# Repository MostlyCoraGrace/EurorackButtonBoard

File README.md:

# EurorackButtonBoard
 A modular, hot-swappable, and patchable, Eurorack-compatible simrig/buttonboard system.
 
 [Follow development on Hackaday](https://hackaday.io/project/199159-eurorack-buttonboard)

# Special Thanks
- A special thanks has to go [PCBWay](https://pcbway.com/g/odjF56), for providing me with free PCBs (and discounts on PCBs when I ask for too many of them, because this project is *voluminous*).
- I would also like to thank my girlfriend, who gave me enough money to buy the first set of electronics I needed to make version 1 of this project. It was expensive.

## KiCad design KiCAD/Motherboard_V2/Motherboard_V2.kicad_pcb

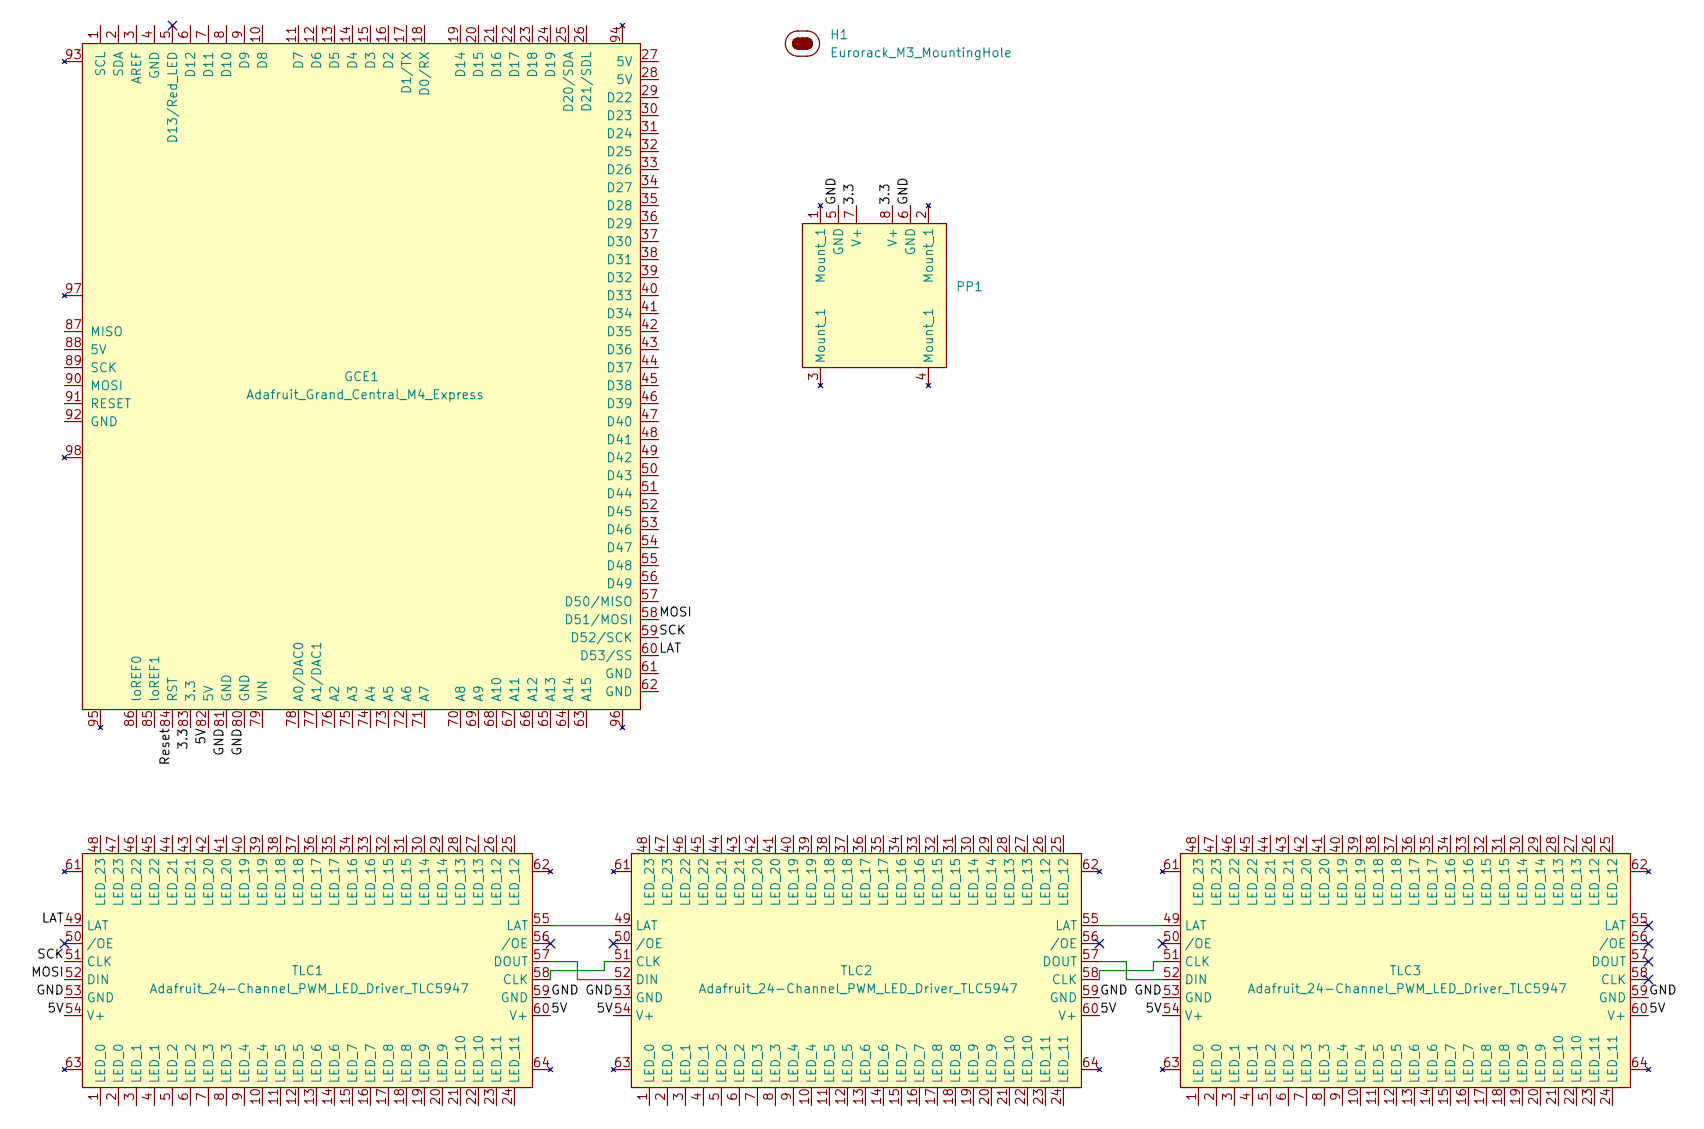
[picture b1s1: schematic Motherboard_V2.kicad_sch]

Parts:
GCE1: Adafruit_Grand_Central_M4_Express
H1: Eurorack_M3_MountingHole; MountingHole_3.2mm_M3
PP1: Adafruit_Perma-Proto_Mint-Tin-Size
TLC1, TLC2, TLC3: Adafruit_24-Channel_PWM_LED_Driver_TLC5947

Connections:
/3.3: GCE1.83 (3.3), PP1.7 (V+), PP1.8 (V+)
/5V: GCE1.82 (5V), TLC1.54 (V+), TLC1.60 (V+), TLC2.54 (V+), TLC2.60 (V+), TLC3.54 (V+), TLC3.60 (V+)
/GND: GCE1.80 (GND), GCE1.81 (GND), PP1.5 (GND), PP1.6 (GND), TLC1.53 (GND), TLC1.59 (GND), TLC2.53 (GND), TLC2.59 (GND), TLC3.53 (GND), TLC3.59 (GND)
/LAT: GCE1.60 (D53/SS), TLC1.49 (LAT)
/MOSI: GCE1.58 (D51/MOSI), TLC1.52 (DIN)
/Reset: GCE1.84 (RST)
/SCK: GCE1.59 (D52/SCK), TLC1.51 (CLK)
unnamed: TLC1.58 (CLK), TLC2.51 (CLK)
unnamed: TLC1.57 (DOUT), TLC2.52 (DIN)
unnamed: TLC1.55 (LAT), TLC2.49 (LAT)
unnamed: TLC2.58 (CLK), TLC3.51 (CLK)
unnamed: TLC2.57 (DOUT), TLC3.52 (DIN)
unnamed: TLC2.55 (LAT), TLC3.49 (LAT)

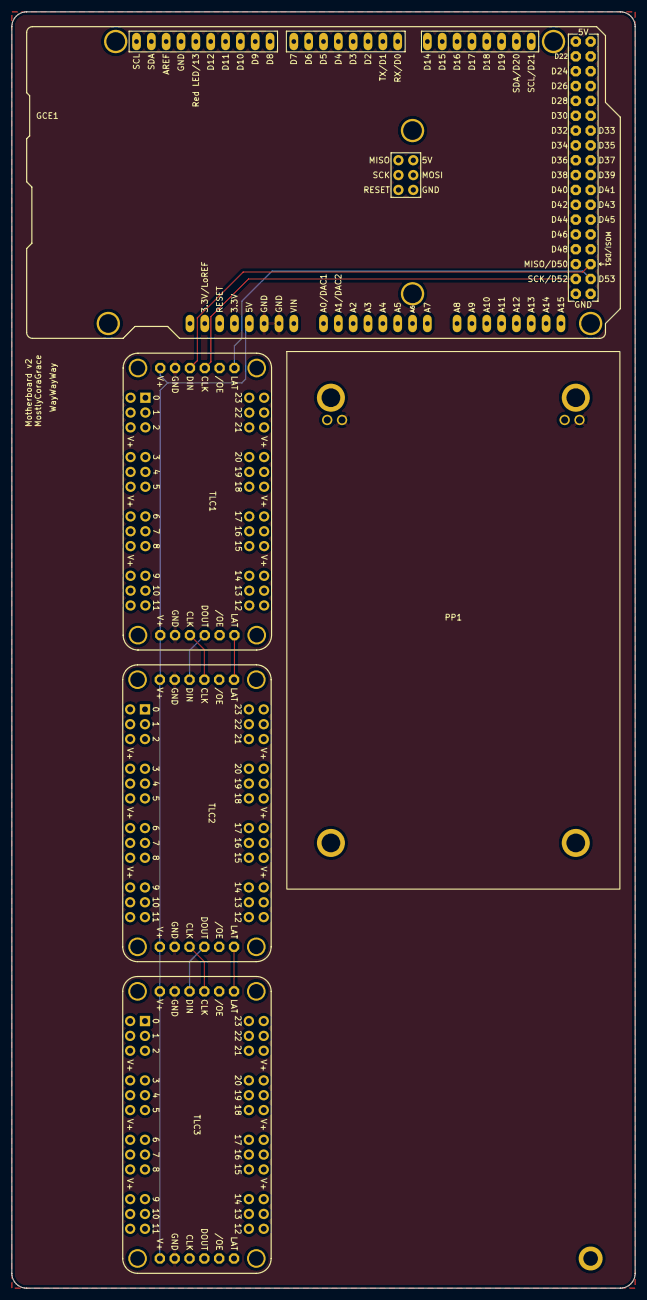
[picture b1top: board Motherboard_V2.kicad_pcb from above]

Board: 2 copper layers, 106.7 x 218.4 mm, 6 parts (0 on the bottom side), 12 nets.

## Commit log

2024-11-02 initialising repo
    started adding some of the parts etc
2024-11-02 adding more modules
    more modules added
2024-11-02 maybe added picture?
    i have no idea what im doing
2024-11-03 adding more modules
    there are so many of them. im getting pretty good at this.
2024-11-03 more modules
    so many
2024-11-03 added 1u toggle switch module
    added 1u toggle switch module
2024-11-03 Create LibraryLocalPaths.txt
    library paths text file so i can just copy-paste them to each kicad project
2024-11-03 Create LICENSE
2024-11-03 updated PCB widths to better conform to Eurorack standards
2024-11-03 added an eurorack-compatible m3 oval mounting hole
2024-11-03 added 3u 3x rotary potentiometer module
2024-11-03 added 3u 4x rotary potentiometer module
2024-11-04 added panel-mounted linear pot schematic symbol
2024-11-04 added panel-mount linear pot footprint
2024-11-04 added linear potentiometer 3u2hp1x module
2024-11-04 added Cherry Switches 2u4hp3x module
2024-11-04 added cherry switches 2u8hp3x2 module
2024-11-04 renamed some modules
2024-11-04 added cherry switches 2u12hp3x3 module
2024-11-04 updated mounting hole to have its ref and silkscreen to the left by default
2024-11-04 added horizontal toggle switch drawing to better visualise placement
2024-11-04 added cherry switch 2u15hp3x4 module
2024-11-04 added rotary potentiometer 2u4hp2x module
2024-11-04 added rotary potentiometer 2u6hp2x module
2024-11-04 added toggle switch 2u3hp3x module
2024-11-04 updated visualisation of some components
2024-11-04 added large panel-mount analog joystick symbol
2024-11-04 added large panel-mount analog joystick footprint
2024-11-04 added large joystick 2u12hp1x module
2024-11-05 updated linear potentiometer symbols for 45mm and 75mm variants
2024-11-05 updated linear potentiometer footprints for 45mm and 75mm variants
2024-11-05 added cherry switches 1u4hp1x module
2024-11-05 added linear potentiometer 2u2hp1x module
2024-11-05 added cherry switches 1u8hp1x3 module
2024-11-05 added cherry switches 1u12hp1x3 module
2024-11-05 fixed silkscreen on cherryswitches_1u12hp1x3 module
2024-11-05 added cherry switches 1u15hp1x4 module
2024-11-05 added blank 2u1hp module
2024-11-05 added blank 2u2hp module
2024-11-05 fixed blank 2u1hp screw mount silkscreens
2024-11-05 added blank 2u3hp module
2024-11-05 added blank 2u4hp module
2024-11-05 added blank 2u8hp module
2024-11-05 added blank 1u1hp module
2024-11-05 added blank 1u2hp module
2024-11-05 added 1u3hp module
2024-11-05 added blank 1u4hp module
2024-11-05 added blank 1u8hp module
2024-11-05 added eurorack specs to readme
2024-11-05 added blank 3u1hp module
2024-11-05 added blank 3u2hp module
2024-11-05 added blank 3u3hp module
2024-11-05 added blank 3u4hp module
2024-11-05 added blank 3u8hp module
2024-11-05 visualisation iteration
2024-11-05 added JLCPCB gerber generation settings for blank 1u1hp module
2024-11-05 added gerbers for more modules
2024-11-05 gerberssss
2024-11-05 added itsybitsy 1u7hp1x module
2024-11-05 added itsybitsy panel mount vertical adapter pcb
2024-11-06 added a mechanical solder pad symbol for easier joint-making
2024-11-06 added a 2-part 3u to 3x 1u adapter pcb
2024-11-06 added silkscreen to 3u adapter modules
2024-11-06 added two-part 2u-to-2x1u adapter module pcbs
2024-11-06 iunno
2024-11-06 added alternate smaller 5hp variant of rotary potentiometer 3u5hp3x module
2024-11-07 added zipped PCB gerber files to gitignore
2024-11-07 updated the cherry switches footprint so that the key silhouette is just a f.fab drawing and not an actual margin that affects copper traces
2024-11-07 updated cherry 5x4 module with copper fills and no front silkscreen text for a cleaner look and maybe better structural rigidity
2024-11-07 deleted test gerbers
2024-11-07 blender visualisation iteration
2024-11-07 removed all front silkscreen, and flipped most modules, to make the boards 'cleaner'.
2024-11-08 updated some footprints so they dont interact in unintended ways with copper fills
2024-11-08 added copper fills to every module, to maybe possibly increase structural rigidity.
2024-11-08 updated thumb
2024-11-10 added logs
2024-11-10 added PCBWay print identification silkscreen text to each component
2024-11-10 visualization iteration
2024-11-14 working on diagram
2024-11-14 added fp-info-cache to gitignore
2024-11-14 moved the eurorack module dimensions to the docs folder, added module dimensions diagram
2024-11-14 added module dimensions diagram to readme
2024-11-23 fixed diagram showing the wrong measurement for pcb-rail clearance
2024-11-26 added joystick_xl circuitpython library files
2024-11-28 visualization iteration.
2024-11-30 preliminary firmware testing
2024-12-29 code
2024-12-29 code progress. added more buttons, and figured out rotary encoders
2025-01-03 microcontroller code updates. added neokey matrix code
2025-02-22 adding logs
2025-03-02 added more components to the libraries
2025-03-02 added a two-part 1U switch module with an LED
2025-03-05 library update
2025-03-05 toggle switch v2 updates
2025-03-05 log pics update
2025-03-06 updated thumbnail
2025-03-06 removed crude diagram from readme
2025-03-06 added link to hackaday log in readme
2025-03-10 fixed mounting hole positioning for ToggleSwitch_1U7HP1x_A
2025-03-10 updated the panel-mounted LED footprint to account for a slightly larger hex nut
2025-05-26 visualizasation iteration
2025-06-14 visualization iteration made 3 different 60hp setups
2025-06-22 visualisation iteration. slowly coming together with a design that makes sense for each module
2025-07-04 visualisation iteration.
2025-07-06 render of the visualisation, for funsies
2025-12-21 starting to populate the V2 panels in KiCAD. Cleared out the old V1 panels.
2025-12-21 added gitignore rule for open spreadsheet lock files
2025-12-22 added 1U to 3U adapter board kicad files
2025-12-22 added a new symbol/footprint for the t80 toggle switch with an m6.35 mounting hole
2025-12-23 adding more modules to kicad
2025-12-23 add more modules
2025-12-23 fixed new 6.35mm toggle switch footprint. the lil nubbin it had for the cutout would have caused issues with the switch in other orientations. i thought i was being clever, but i was just shooting my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
2025-12-23 adding more modules
2025-12-23 added more lengths of module to the module lengths table
2025-12-23 moved all footprints' reference texts to be on the back silkscreen layer, because thats where i want them and it was getting tedious moving them there manually every time i made a pcb
2025-12-23 added a 16mm panel-mounted momentary push button to the symbols and footprints libraries
2025-12-23 added a new 6mm panel-mount push-button footprint/symbol, and updated the m16, m6, and m6.35 footprints to better differentiate between them
2025-12-23 adding some push button modules to kicad
2025-12-23 added a paddle switch footprint set
2025-12-23 more module add
2025-12-24 added a large knob footprint for the top panels
2025-12-24 updated the 25mm handle for 1u modules. its footprints and symbols now correctly link to where i get them, and have descriptions for what each of its A and B parts do
2025-12-24 added a t18 knob symbol and footprint
2025-12-24 added a large knob and a rotary encoder module
2025-12-25 added an 1u rotary encoder module
2025-12-25 updated the rotary selector footprint to have the notch it requires to be mounted correctly.
2025-12-25 added some rotary selector modules
2025-12-25 added a top-panel footprint for the 45mm slide pot
2025-12-25 added 45mm 1u slide pot module
2025-12-25 added a 45mm slide pot with handle module
2025-12-25 added a 2x 45mm slide pot module
2025-12-25 another module add
2025-12-26 added rocker switch top panel footprint
2025-12-26 added rocker switch module
2025-12-26 added 2u1hp blank
2025-12-26 added the rest of the 2u blanks
2025-12-26 adding more 2u cherry switch modules
2025-12-27 added 2u 4x3 cherry switch module
2025-12-27 added a new 2u 60mm handle footprint/symbol pair
2025-12-27 added the top panel footprint/symbol for the large joystick
2025-12-27 fixed the silkscreen on the joystick top footprint
2025-12-27 added large joystick module
2025-12-28 added a 1hp and a 2hp 2u-to-1u adapter modules
2025-12-28 fixed silkscreens on adapter_2u2hpbv2
2025-12-28 added a variant of the adapter_2u2hpbv2 which has a handle
2025-12-28 added a 2u to 30 adapter module
2025-12-28 add slidepot_45mm_2u4hp1x1 module
2025-12-28 added slide pot 45mm 2u6hp1x1 with handle module
2025-12-28 added more 2u slide pot modules
2025-12-28 added a top footprint for the illuminated toggle switch
2025-12-28 added illuminated toggle switch module
2025-12-28 added another illuminated toggle switch module, this time with a handle
2025-12-28 added some more momentary button modules
2025-12-29 added 3U blanks
2025-12-29 added 3U 100mmm handle footprints
2025-12-29 added 3u 100mm handle symbols
2025-12-29 added a 3u 2x75mm slide pot module
2025-12-29 added 2x 75mm slide pot module
2025-12-30 moved the silkscreen to the same side as the pad on the mechanical solder pad footprint, since it shouldnt be on the other side
2025-12-30 added mechanical solder pads to the adapter boards that were missing them. woops!
2025-12-30 fixed up silkscreens on some boards
2025-12-30 added new 3u adapter module
2025-12-31 updated the 1u->3u adapter board to work better
2025-12-31 added module part
2025-12-31 adjusted 2u->3u adapter module
2025-12-31 added 3u 3x large knob module
2025-12-31 added 2u 1x2 large knob module
2025-12-31 add module
2026-01-04 starting to flesh out the BOM list
2026-01-04 changed the eurorack m3 mount footprint to be plated through-hole, for extra rigidity
2026-01-04 added a 12hp perma proto module
2026-01-05 updated all modules to use plated through-holes wherever possible
2026-01-05 bom updates
2026-01-08 added the special thanks section to the readme
2026-01-09 adding parts to the bom
2026-01-09 add missing log pictures
2026-01-22 added adafruit grand central m4 express footprint and schematic
2026-01-23 added silkscreens to new adafruit modules
2026-01-23 add external reference projects
2026-01-23 add first prototype for a motherboard
2026-01-24 noodling
2026-01-25 changed the 1u handle to have variable screw hole distance, since the new handles suck so much
2026-01-25 expanded tolerances for the illuminated toggle switch, since it also sucks
2026-01-25 update pcb
2026-01-25 add silkscreens to grand central m4
2026-01-25 update 24-channel pwm led driver symbol
2026-01-25 update grand central schematic to have the mount points in it
2026-01-26 update footprint
2026-01-26 add perma-proto footprint
2026-01-26 motherboard tinkering
2026-01-26 motherboard noodling
2026-01-27 adjusted positioning of the slide pots in 3u5hp2x1 to fix tolerance issues
